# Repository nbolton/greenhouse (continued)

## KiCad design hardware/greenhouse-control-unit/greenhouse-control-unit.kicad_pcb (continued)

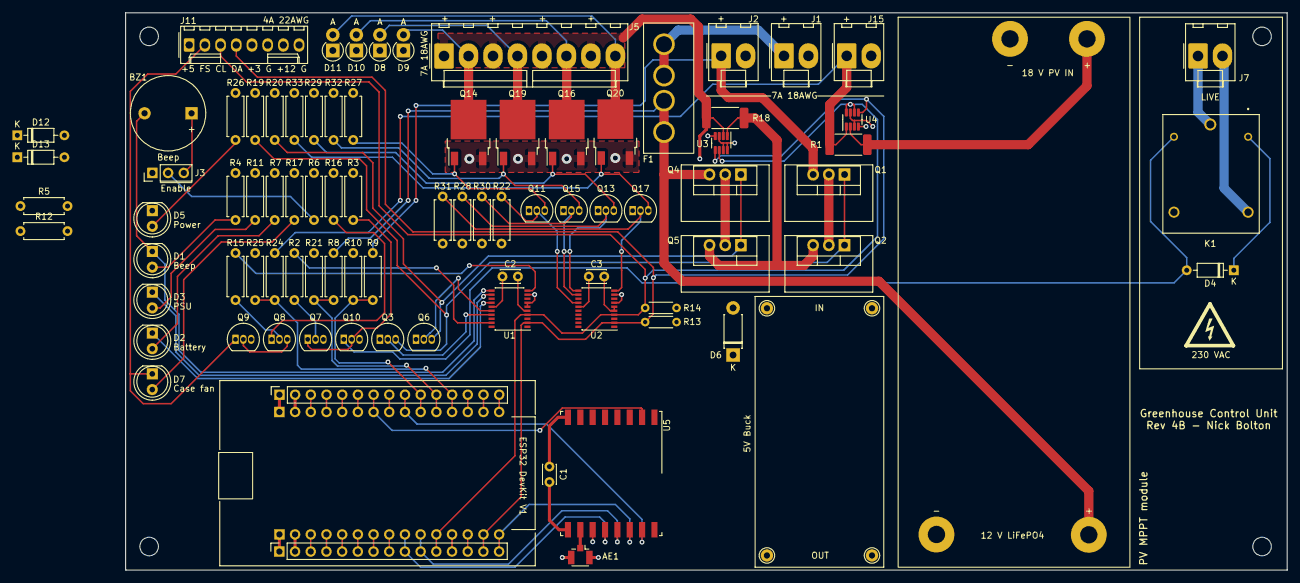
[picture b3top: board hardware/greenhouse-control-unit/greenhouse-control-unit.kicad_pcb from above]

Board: 4 copper layers, 188.0 x 90.2 mm, 89 parts (0 on the bottom side), 62 nets.

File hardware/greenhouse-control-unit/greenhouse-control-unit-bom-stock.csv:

Comment,Stock,Designator,Footprint,LCSC Part #
"2kΩ? Buzzer, polarized",5,BZ1,Buzzer_12x9.5RM7.6,
"10nF Unpolarized capacitor, small symbol",++,"C2,C3",C_Disc_D4.7mm_W2.5mm_P5.00mm,
LED Light emitting diode,++,"D1,D2,D3,D5,D7",LED_D5.0mm,
D Diode,++,D4,D_DO-35_SOD27_P7.62mm_Horizontal,
D Diode,++,D6,D_DO-41_SOD81_P7.62mm_Horizontal,
D Diode,++,"D8,D9,D10,D11",D_DO-41_SOD81_P2.54mm_Vertical_AnodeUp,
Fuse Fuse,++,F1,Fuse_3522-2_L,
"Molex_KK-396_01x02 Generic connector, single row, 01x02, script generated",10?,"J1,J2,J7,J15",Molex_KK-396_1x02_P3.96mm_Vertical,
"Beep_Jumper Generic connector, single row, 01x03, script generated",++,J3,PinHeader_1x03_P2.54mm_Vertical,
"PV MPPT module Generic connector, single row, 01x04, script generated",1,J4,MPPT-10A-Module,
"Conn_01x08_Pin Generic connector, single row, 01x08, script generated",-,J5,Molex_KK-396_1x08_P3.96mm_Vertical,
"5V Buck Generic connector, single row, 01x04, script generated",1?,J6,Buck_Module,
"Conn_01x09 Generic connector, single row, 01x09, script generated",-,J8,PinSocket_1x09_P2.54mm_Vertical,
"Conn_01x05_Female Generic connector, single row, 01x05, script generated",-,J9,PinSocket_1x05_P2.54mm_Vertical,
"Conn_ESP32_DevKitV1_Female Generic connector, single row, 01x13, script generated (kicad-library-utils/schlib/autogen/connector/)",-,J10,PinSocket_ESP32_DevKitV1,
"Molex_254_1x08 Generic connector, single row, 01x12, script generated (kicad-library-utils/schlib/autogen/connector/)",10?,J11,Molex_KK-254_AE-6410-08A_1x08_P2.54mm_Vertical,
"SRD-12VDC-SL-C Sanyo SRD relay, Single Pole Miniature Power Relay,",5,K1,Relay_SRD-12VDC-SL-C,
"IRF4905 -74A Id, -55V Vds, Single P-Channel HEXFET Power MOSFET, 20mOhm Ron, TO-220AB",50?,"Q1,Q2,Q4,Q5",TO-220-3_Vertical,
"2N7000 0.2A Id, 200V Vds, N-Channel MOSFET, 2.6V Logic Level, TO-92",10?,"Q3,Q6,Q11,Q13,Q15,Q17",TO-92_Inline,
"BC547 0.1A Ic, 45V Vce, Small Signal NPN Transistor, TO-92",10?,"Q7,Q8,Q10",TO-92_Inline,
"BC337 0.8A Ic, 45V Vce, NPN Transistor, TO-92",10?,Q9,TO-92_Inline,
"STD30NF06LT4 N-MOSFET transistor, gate/drain/source",0,"Q14,Q16,Q19,Q20",TO-252-2,
"0R001 Resistor, US symbol",0,"R1,R18",R_2512_6332Metric_Pad1.40x3.35mm_HandSolder,
"33k Resistor, US symbol",50?,"R2,R15",R_Axial_DIN0207_L6.3mm_D2.5mm_P7.62mm_Horizontal,
"1k Resistor, US symbol",50?,"R3,R16",R_Axial_DIN0207_L6.3mm_D2.5mm_P7.62mm_Horizontal,
"2k Resistor, US symbol",50?,"R4,R7,R11,R17",R_Axial_DIN0207_L6.3mm_D2.5mm_P7.62mm_Horizontal,
"100R Resistor, US symbol",50?,R6,R_Axial_DIN0207_L6.3mm_D2.5mm_P7.62mm_Horizontal,
"1M Resistor, US symbol",50?,"R8,R9,R24",R_Axial_DIN0207_L6.3mm_D2.5mm_P7.62mm_Horizontal,
"100k Resistor, US symbol",50?,"R10,R21,R25",R_Axial_DIN0207_L6.3mm_D2.5mm_P7.62mm_Horizontal,
"10k Resistor, US symbol",50?,"R13,R14",R_Axial_DIN0204_L3.6mm_D1.6mm_P5.08mm_Horizontal,
"10k Resistor, US symbol",50?,"R19,R22,R23,R26,R27,R28,R29,R30,R31,R32,R33",R_Axial_DIN0207_L6.3mm_D2.5mm_P7.62mm_Horizontal,
"PCF8574 8 Bit Port/Expander to I2C Bus, DIP/SOIC-16",0,"U1,U2",SOIC-16W_7.5x10.3mm_P1.27mm,
"INA219 Zero-Drift, Bidirectional Current/Power Monitor (0-26V) With I2C Interface, SOT-23-8",0,"U3,U4",SOT-23-8,

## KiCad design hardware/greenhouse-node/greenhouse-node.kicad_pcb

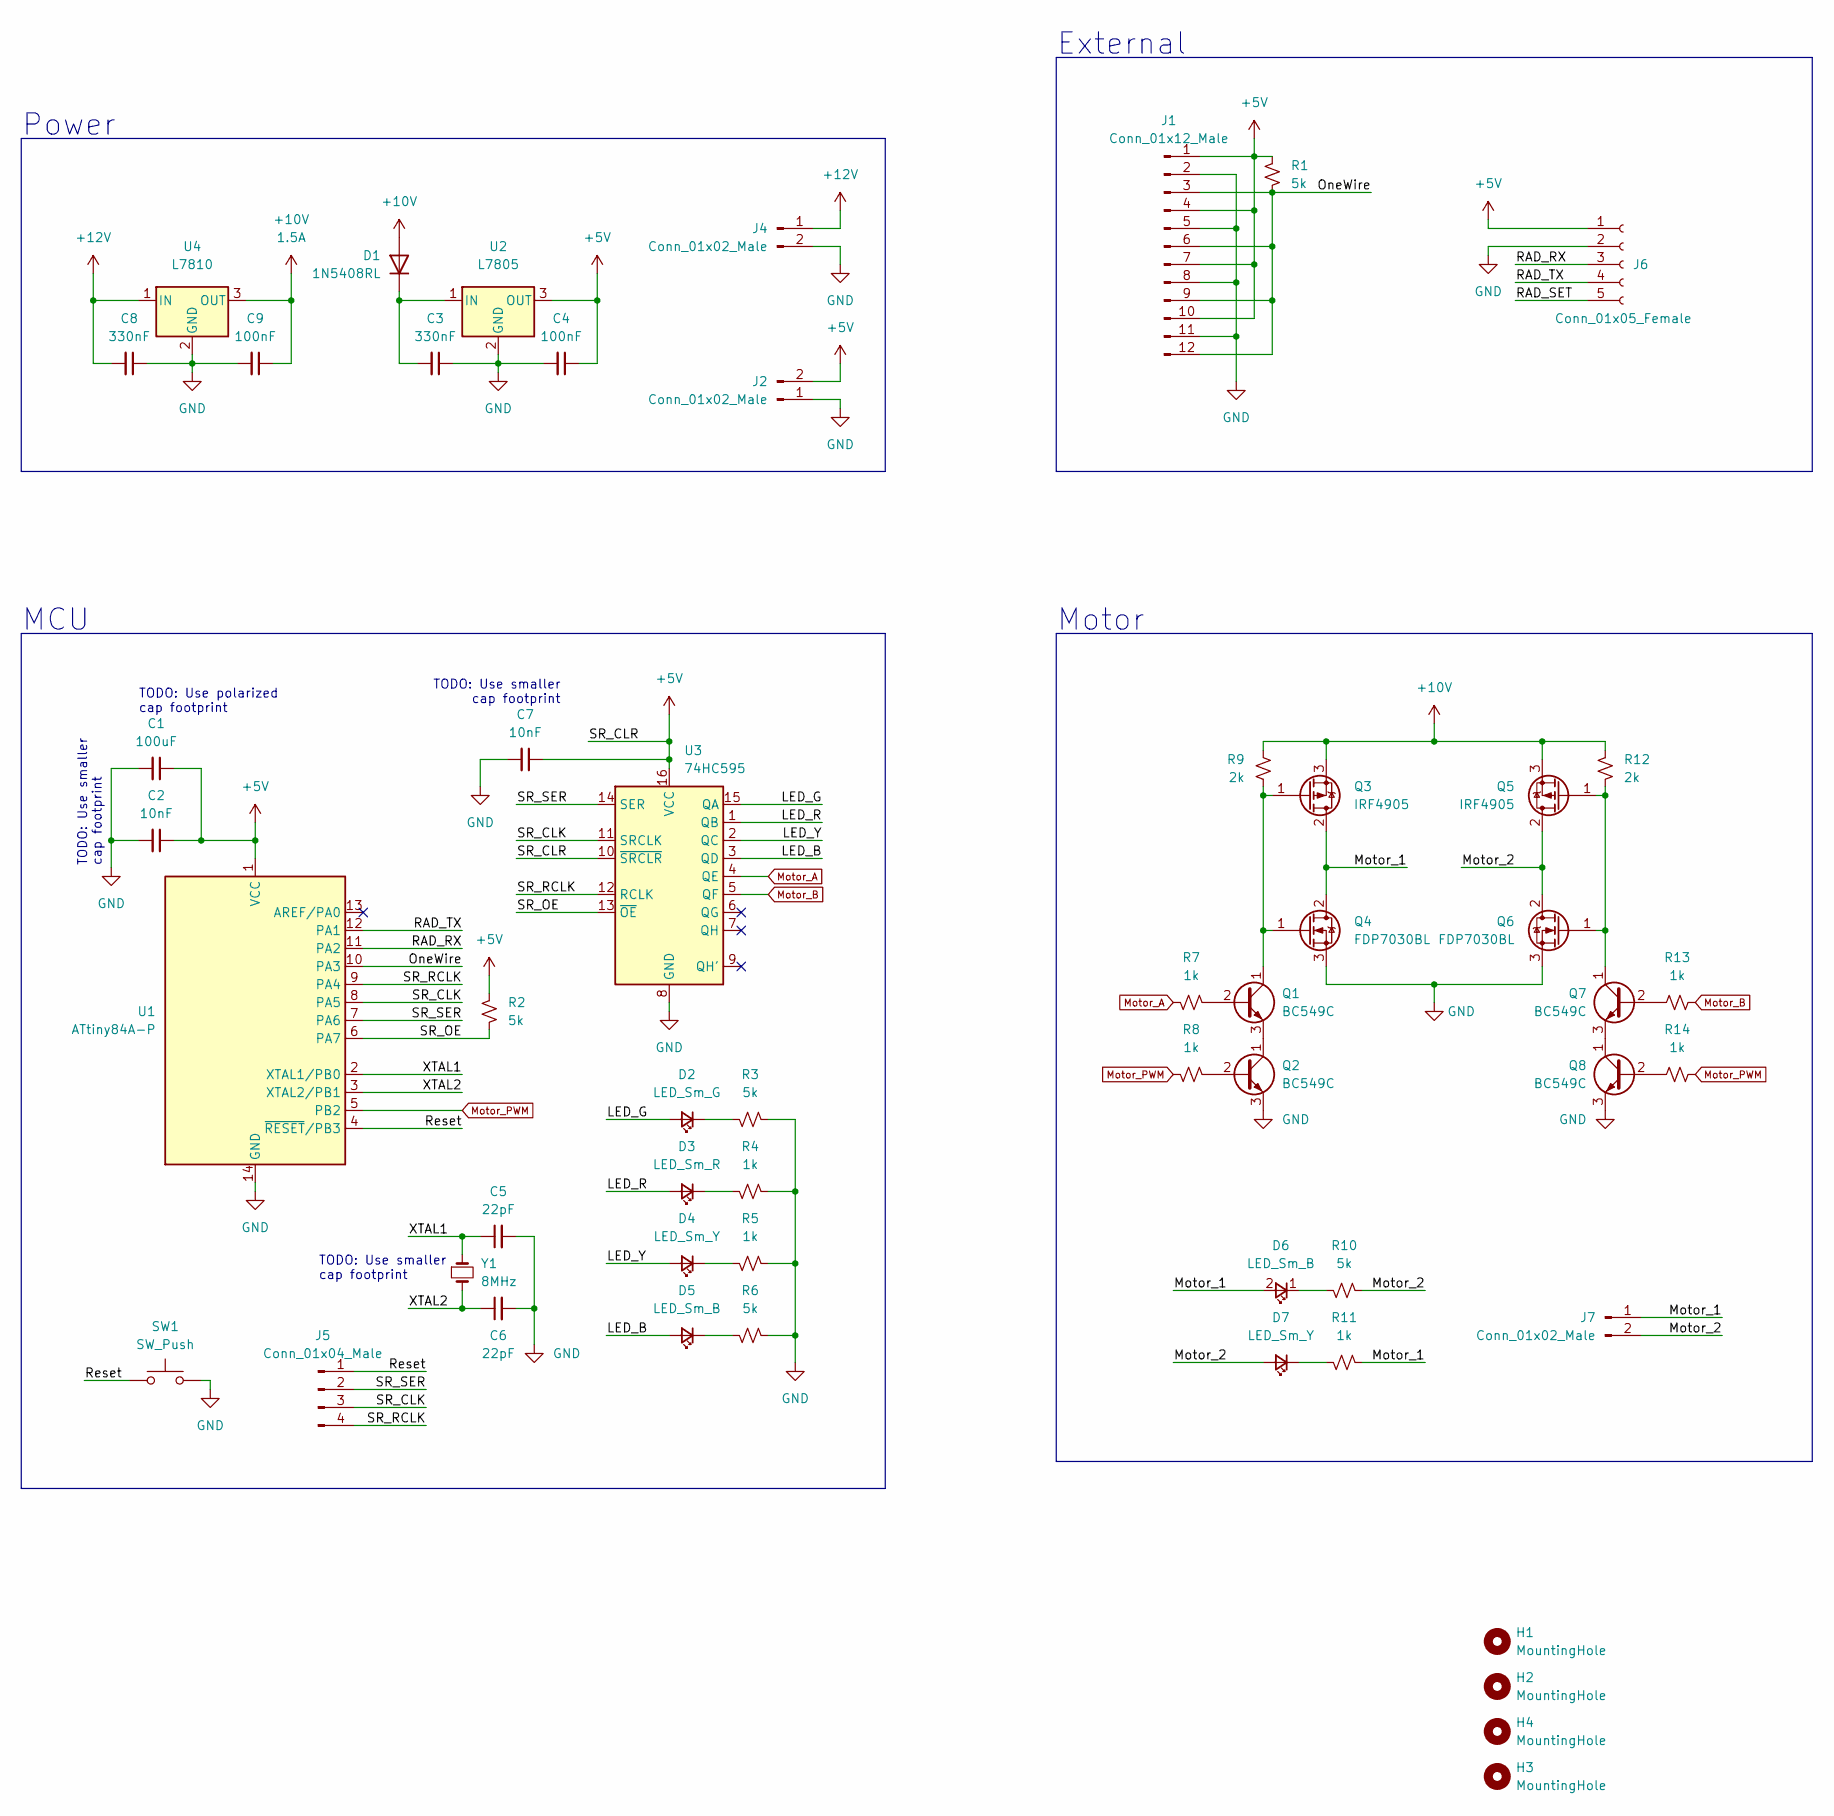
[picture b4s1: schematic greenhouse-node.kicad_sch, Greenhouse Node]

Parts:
C1: 100uF; C_Radial_D5.0mm_H7.0mm_P2.00mm
C2, C7: 10nF; C_Disc_D4.7mm_W2.5mm_P5.00mm
C3, C8: 330nF; C_Disc_D4.7mm_W2.5mm_P5.00mm
C4, C9: 100nF; C_Disc_D4.7mm_W2.5mm_P5.00mm
C5, C6: 22pF; C_Disc_D4.7mm_W2.5mm_P5.00mm
D1: 1N5408RL; D_A-405_P7.62mm_Horizontal
D2: LED_Sm_G; LED_D3.0mm
D3: LED_Sm_R; LED_D3.0mm
D4, D7: LED_Sm_Y; LED_D3.0mm
D5, D6: LED_Sm_B; LED_D3.0mm
H1, H2, H3, H4: MountingHole; MountingHole_3.2mm_M3
J1: Conn_01x12_Male; Molex_KK-254_AE-6410-12A_1x12_P2.54mm_Vertical
J2: Conn_01x02_Male; JST_XH_B2B-XH-A_1x02_P2.50mm_Vertical
J4, J7: Conn_01x02_Male; Molex_KK-396_A-41791-0002_1x02_P3.96mm_Vertical
J5: Conn_01x04_Male; JST_XH_B4B-XH-A_1x04_P2.50mm_Vertical
J6: Conn_01x05_Female; PinSocket_1x05_P2.54mm_Vertical
Q1, Q2, Q7, Q8: BC549C; TO-92_Inline
Q3, Q5: IRF4905; TO-220-3_Horizontal_TabDown
Q4, Q6: FDP7030BL; TO-220-3_Horizontal_TabDown
R1, R2, R3, R6, R10: 5k; R_Axial_DIN0207_L6.3mm_D2.5mm_P7.62mm_Horizontal
R4, R5, R7, R8, R11, R13, R14: 1k; R_Axial_DIN0207_L6.3mm_D2.5mm_P7.62mm_Horizontal
R9, R12: 2k; R_Axial_DIN0207_L6.3mm_D2.5mm_P7.62mm_Horizontal
SW1: SW_Push; SW_PUSH_6mm
U1: ATtiny84A-P; DIP-14_W7.62mm_Socket
U2: L7805; TO-220-3_Horizontal_TabDown
U3: 74HC595; DIP-16_W7.62mm_Socket
U4: L7810; TO-220-3_Horizontal_TabDown
Y1: 8MHz; Crystal_HC49-4H_Vertical

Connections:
+5V: C1.1, C2.1, C4.1, C7.1, J1.1, J1.4, J1.7, J1.10, J2.2, J6.1, R1.1, R2.1, U1.1 (VCC), U2.3 (OUT), U3.10 (~SRCLR), U3.16 (VCC)
+10V: C9.1, D1.2 (A), Q3.3 (S), Q5.3 (S), R9.2, R12.2, U4.3 (OUT)
+12V: C8.2, J4.1, U4.1 (IN)
/LED_B: D5.2 (A), U3.3 (QD)
/LED_G: D2.2 (A), U3.15 (QA)
/LED_R: D3.2 (A), U3.1 (QB)
/LED_Y: D4.2 (A), U3.2 (QC)
/Motor_1: D6.2 (A), J7.1, Q3.2 (D), Q4.2 (D), R11.1
/Motor_2: D7.2 (A), J7.2, Q5.2 (D), Q6.2 (D), R10.1
/OneWire: J1.3, J1.6, J1.9, J1.12, R1.2, U1.10 (PA3)
/RAD_RX: J6.3, U1.11 (PA2)
/RAD_SET: J6.5
/RAD_TX: J6.4, U1.12 (PA1)
/Reset: J5.1, SW1.1, U1.4 (~RESET/PB3)
/SR_CLK: J5.3, U1.8 (PA5), U3.11 (SRCLK)
/SR_OE: R2.2, U1.6 (PA7), U3.13 (~OE)
/SR_RCLK: J5.4, U1.9 (PA4), U3.12 (RCLK)
/SR_SER: J5.2, U1.7 (PA6), U3.14 (SER)
/XTAL1: C5.1, U1.2 (XTAL1/PB0), Y1.1
/XTAL2: C6.1, U1.3 (XTAL2/PB1), Y1.2
GND: C1.2, C2.2, C3.1, C4.2, C5.2, C6.2, C7.2, C8.1, C9.2, J1.2, J1.5, J1.8, J1.11, J2.1, J4.2, J6.2, Q2.3 (E), Q4.3 (S), Q6.3 (S), Q8.3 (E), R3.1, R4.1, R5.1, R6.1, SW1.2, U1.14 (GND), U2.2 (GND), U3.8 (GND), U4.2 (GND)
Motor_A: R7.2, U3.4 (QE)
Motor_B: R13.2, U3.5 (QF)
Motor_PWM: R8.2, R14.2, U1.5 (PB2)
unnamed: C3.2, D1.1 (K), U2.1 (IN)
unnamed: D2.1 (K), R3.2
unnamed: D3.1 (K), R4.2
unnamed: D4.1 (K), R5.2
unnamed: D5.1 (K), R6.2
unnamed: D6.1 (K), R10.2
unnamed: D7.1 (K), R11.2
unnamed: Q1.1 (C), Q3.1 (G), Q4.1 (G), R9.1
unnamed: Q1.2 (B), R7.1
unnamed: Q1.3 (E), Q2.1 (C)
unnamed: Q2.2 (B), R8.1
unnamed: Q5.1 (G), Q6.1 (G), Q7.1 (C), R12.1
unnamed: Q7.2 (B), R13.1
unnamed: Q7.3 (E), Q8.1 (C)
unnamed: Q8.2 (B), R14.1

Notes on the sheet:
Motor
TODO: Use polarized cap footprint
Power
MCU
TODO: Use smaller cap footprint
External

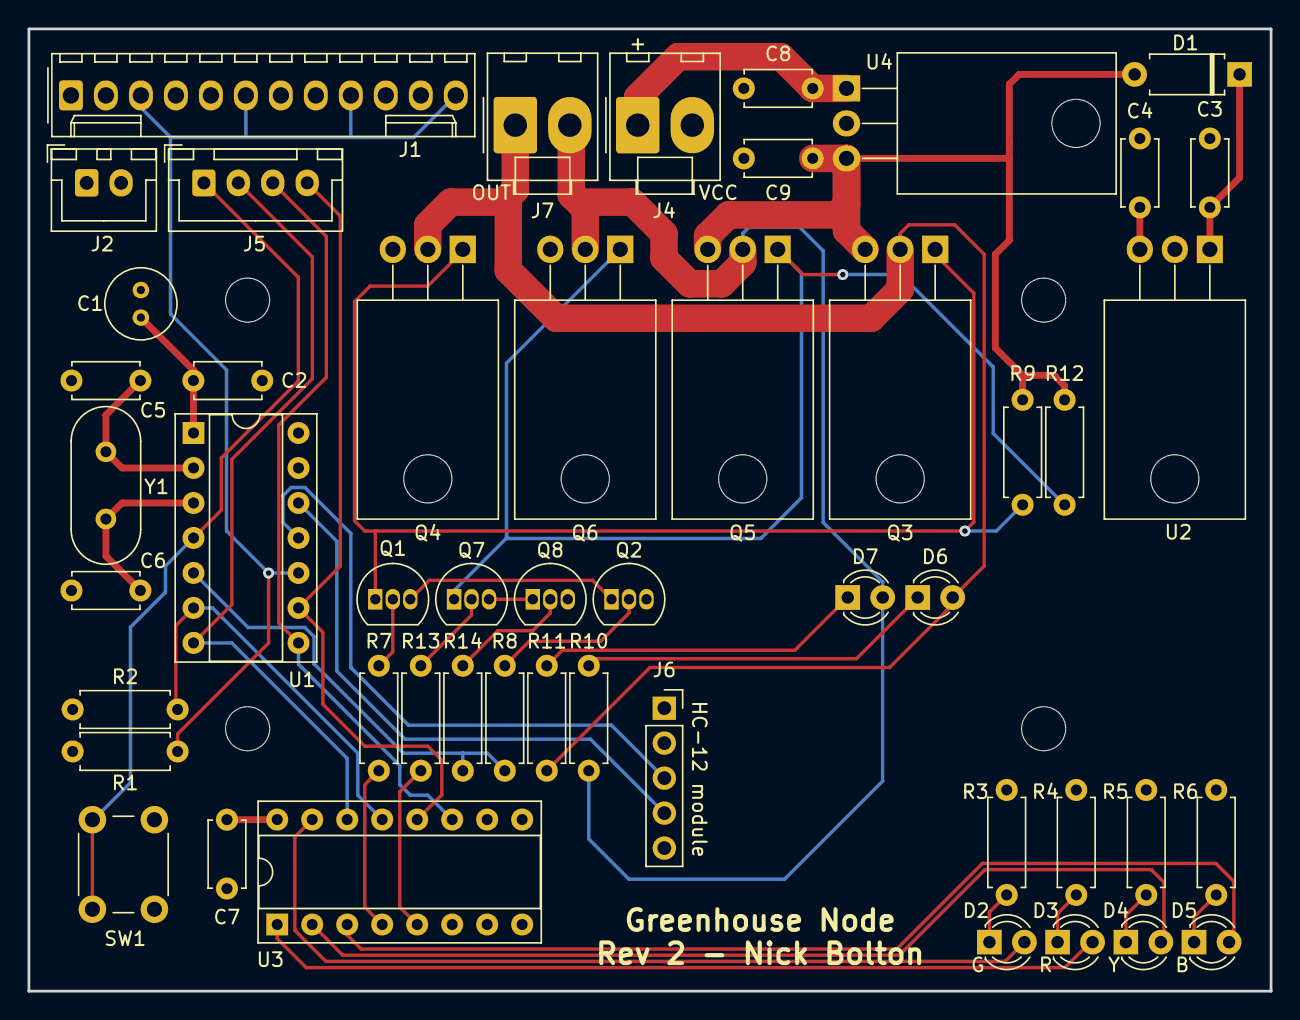
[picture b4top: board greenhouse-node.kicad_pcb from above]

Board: 4 copper layers, 90.2 x 69.8 mm, 54 parts (0 on the bottom side), 38 nets.

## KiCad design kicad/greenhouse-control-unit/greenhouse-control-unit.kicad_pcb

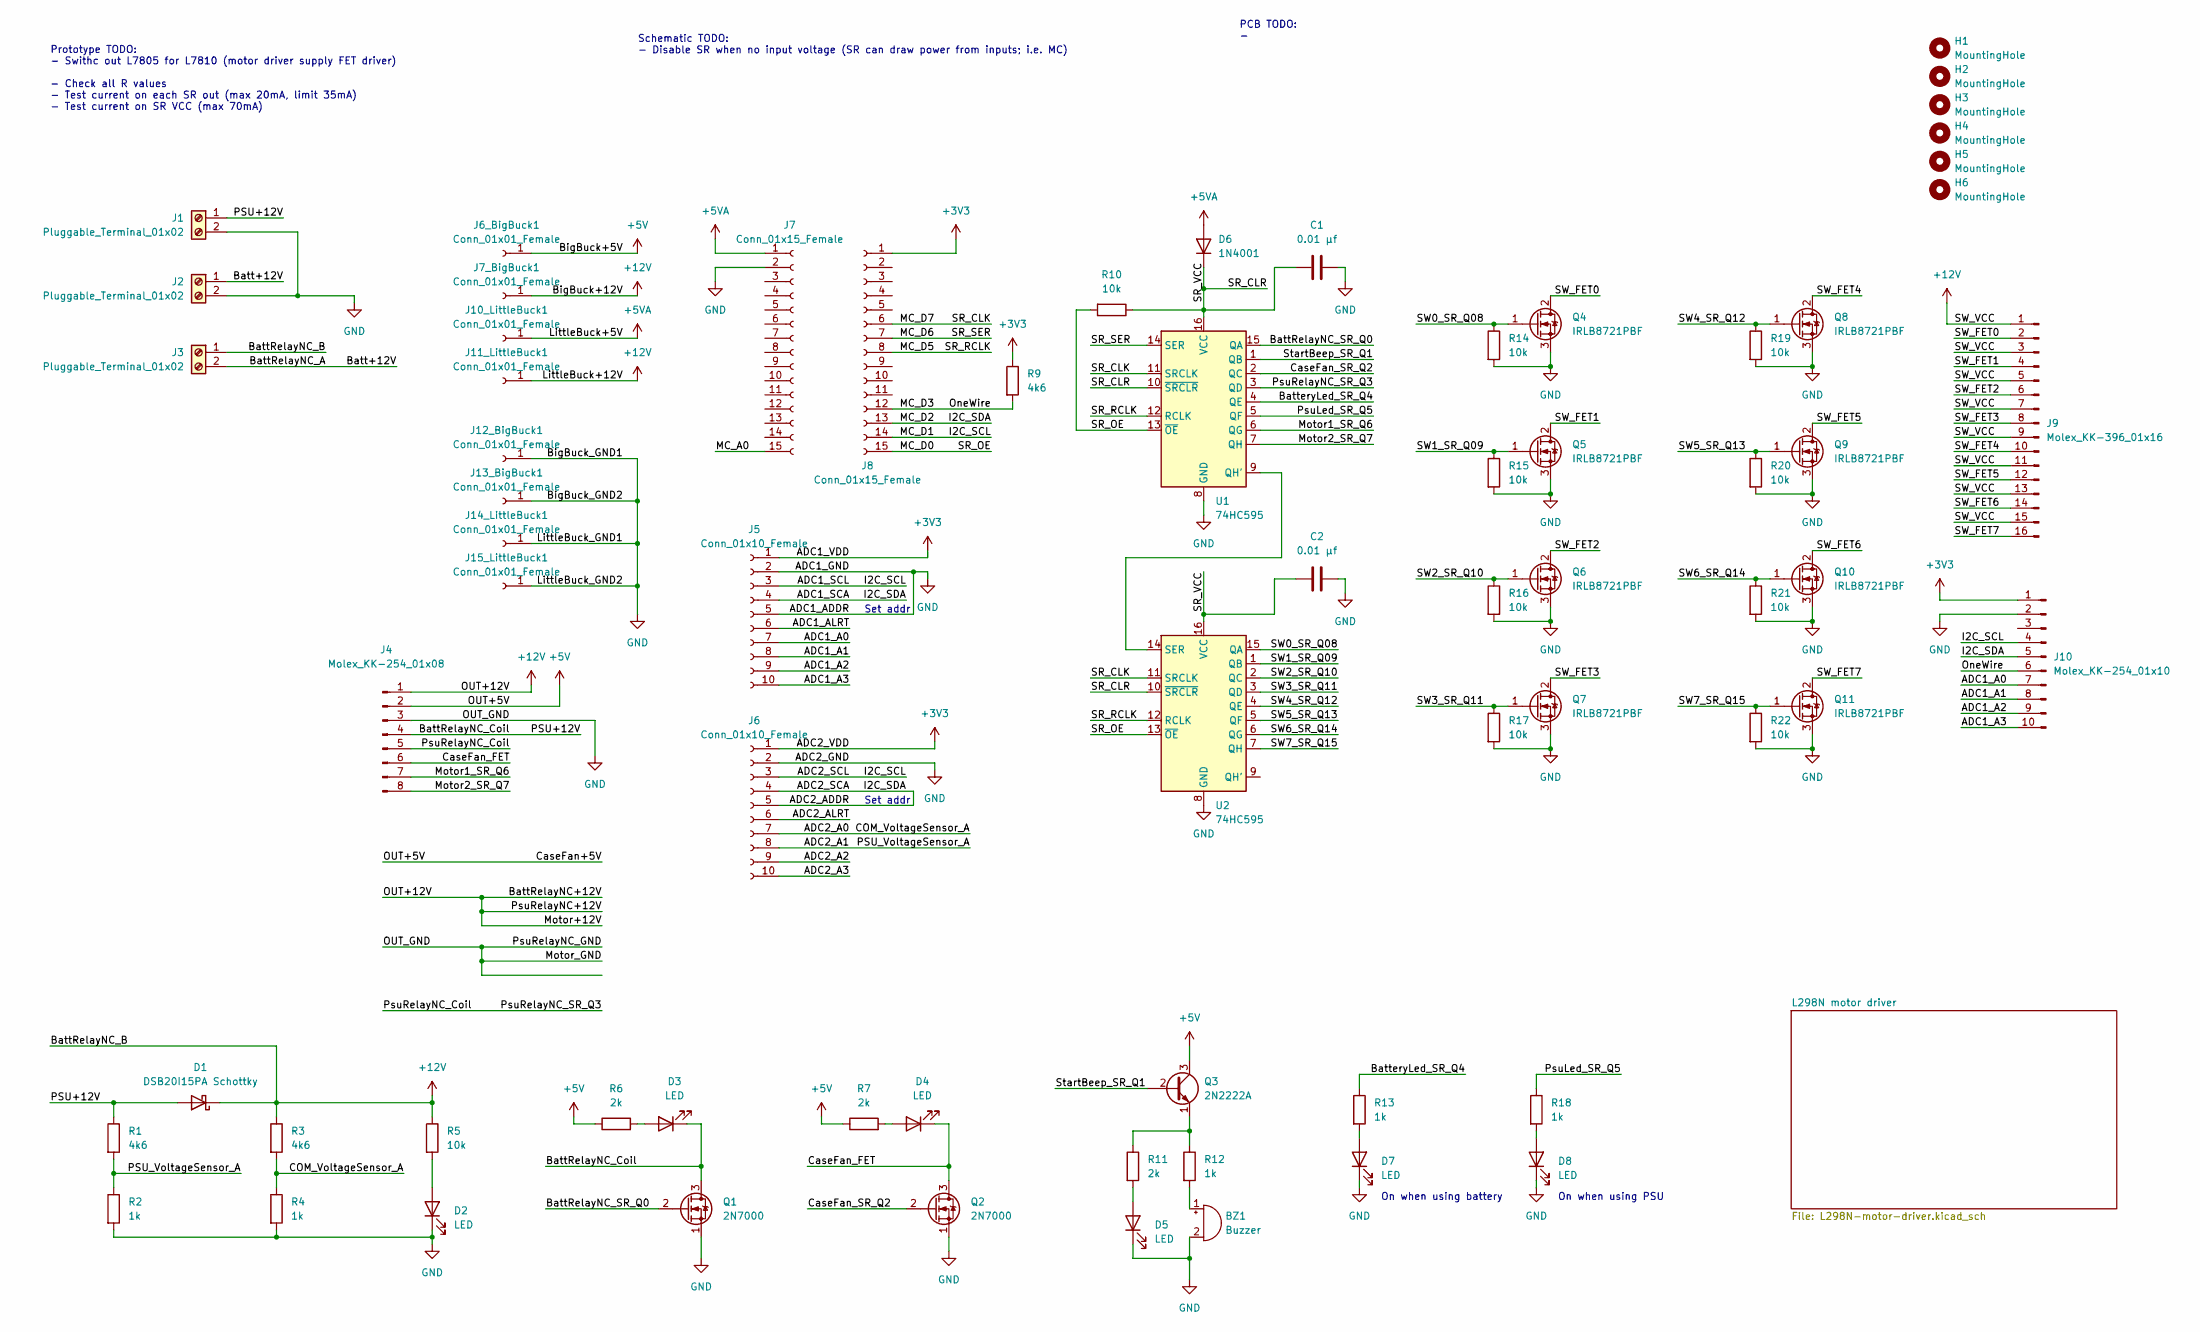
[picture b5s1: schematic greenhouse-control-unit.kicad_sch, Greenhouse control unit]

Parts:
BZ1: Buzzer; Buzzer_12x9.5RM7.6
C1, C2: 0.01 μf; C_Disc_D3.0mm_W1.6mm_P2.50mm
D1: DSB20I15PA Schottky; TO-220-2_Vertical
D2, D3, D4, D5, D7, D8: LED; LED_D5.0mm
D6: 1N4001; D_DO-41_SOD81_P10.16mm_Horizontal
H1, H2, H3, H4, H5, H6: MountingHole; MountingHole_3mm
J1, J2, J3: Pluggable_Terminal_01x02; TerminalBlock_Phoenix_MKDS-1,5-2-5.08_1x02_P5.08mm_Horizont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
J4: Molex_KK-254_01x08; Molex_KK-254_AE-6410-08A_1x08_P2.54mm_Vertical
J5, J6: Conn_01x10_Female; PinSocket_1x10_P2.54mm_Vertical
J6_BigBuck1, J7_BigBuck1, J12_BigBuck1, J13_BigBuck1: Conn_01x01_Female; PinSocket_1x01_P2.54mm_Vertical
J7, J8: Conn_01x15_Female; PinSocket_1x15_P2.54mm_Vertical
J9: Molex_KK-396_01x16; Molex_KK-396_A-41791-0016_1x16_P3.96mm_Vertical
J10: Molex_KK-254_01x10; Molex_KK-254_AE-6410-10A_1x10_P2.54mm_Vertical
J10_LittleBuck1, J11_LittleBuck1, J14_LittleBuck1, J15_LittleBuck1: Conn_01x01_Female; PinHeader_1x01_P2.54mm_Vertical
Q1, Q2: 2N7000; TO-92_Inline
Q3: 2N2222A; TO-92_Inline
Q4, Q5, Q6, Q7, Q8, Q9, Q10, Q11: IRLB8721PBF; TO-220-3_Horizontal_TabDown
R1, R3, R9: 4k6; R_Axial_DIN0207_L6.3mm_D2.5mm_P7.62mm_Horizontal
R2, R4, R12, R13, R18: 1k; R_Axial_DIN0207_L6.3mm_D2.5mm_P7.62mm_Horizontal
R5: 10k; R_Axial_DIN0207_L6.3mm_D2.5mm_P7.62mm_Horizontal
R6, R7, R11: 2k; R_Axial_DIN0207_L6.3mm_D2.5mm_P7.62mm_Horizontal
R10, R14, R15, R16, R17, R19, R20, R21, R22: 10k; R_Axial_DIN0204_L3.6mm_D1.6mm_P5.08mm_Horizontal
U1, U2: 74HC595; DIP-16_W7.62mm_Socket

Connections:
+3V3: J5.1, J6.1, J8.1, J10.1, R9.1
+5V: J4.2, J6_BigBuck1.1, Q3.3 (C), R6.1, R7.1; also elsewhere on the board
+5VA: D6.2 (A), J7.1, J10_LittleBuck1.1
+12V: D1.1 (K), J3.1, J4.1, J7_BigBuck1.1, J9.1, J9.3, J9.5, J9.7, J9.9, J9.11, J9.13, J9.15, J11_LittleBuck1.1, R3.1, R5.1; also elsewhere on the board
/ADC1_A0: J5.7, J10.7
/ADC1_A1: J5.8, J10.8
/ADC1_A2: J5.9, J10.9
/ADC1_A3: J5.10, J10.10
/ADC1_ALRT: J5.6
/ADC1_SCA: J5.4, J6.4, J6.5, J8.13, J10.5
/ADC1_SCL: J5.3, J6.3, J8.14, J10.4
/ADC2_A0: J6.7, R3.2, R4.1
/ADC2_A1: J6.8, R1.2, R2.1
/ADC2_A2: J6.9
/ADC2_A3: J6.10
/ADC2_ALRT: J6.6
/Batt+12V: J2.1, J3.2
/BattRelayNC_Coil: D1.2 (A), D3.1 (K), J1.1, J4.4, Q1.3 (D), R1.1
/BattRelayNC_SR_Q0: Q1.2 (G), U1.15 (QA)
/BatteryLed_SR_Q4: R13.1, U1.4 (QE)
/CaseFan_FET: D4.1 (K), J4.6, Q2.3 (D)
/CaseFan_SR_Q2: Q2.2 (G), U1.2 (QC)
/MC_A0: J7.15
/MC_D0: J8.15, R10.2, U1.13 (~OE), U2.13 (~OE)
/MC_D3: J8.12, J10.6, R9.2
/MC_D5: J8.8, U1.12 (RCLK), U2.12 (RCLK)
/MC_D6: J8.7, U1.14 (SER)
/MC_D7: J8.6, U1.11 (SRCLK), U2.11 (SRCLK)
/Motor1_SR_Q6: J4.7, U1.6 (QG)
/Motor2_SR_Q7: J4.8, U1.7 (QH)
/PsuLed_SR_Q5: R18.1, U1.5 (QF)
/PsuRelayNC_Coil: J4.5, U1.3 (QD)
/SR_CLR: C1.1, C2.1, D6.1 (K), R10.1, U1.10 (~SRCLR), U1.16 (VCC), U2.10 (~SRCLR), U2.16 (VCC)
/SW0_SR_Q08: Q4.1 (G), R14.1, U2.15 (QA)
/SW1_SR_Q09: Q5.1 (G), R15.1, U2.1 (QB)
/SW2_SR_Q10: Q6.1 (G), R16.1, U2.2 (QC)
/SW3_SR_Q11: Q7.1 (G), R17.1, U2.3 (QD)
/SW4_SR_Q12: Q8.1 (G), R19.1, U2.4 (QE)
/SW5_SR_Q13: Q9.1 (G), R20.1, U2.5 (QF)
/SW6_SR_Q14: Q10.1 (G), R21.1, U2.6 (QG)
/SW7_SR_Q15: Q11.1 (G), R22.1, U2.7 (QH)
/SW_FET0: J9.2, Q4.2 (D)
/SW_FET1: J9.4, Q5.2 (D)
/SW_FET2: J9.6, Q6.2 (D)
/SW_FET3: J9.8, Q7.2 (D)
/SW_FET4: J9.10, Q8.2 (D)
/SW_FET5: J9.12, Q9.2 (D)
/SW_FET6: J9.14, Q10.2 (D)
/SW_FET7: J9.16, Q11.2 (D)
/StartBeep_SR_Q1: Q3.2 (B), U1.1 (QB)
GND: BZ1.2 (+), C1.2, C2.2, D2.1 (K), D5.1 (K), D7.1 (K), D8.1 (K), J1.2, J2.2, J4.3, J5.2, J5.5, J6.2, J7.2, J10.2, J12_BigBuck1.1, J13_BigBuck1.1, J14_LittleBuck1.1, J15_LittleBuck1.1, Q1.1 (S), Q2.1 (S), Q4.3 (S), Q5.3 (S), Q6.3 (S), Q7.3 (S), Q8.3 (S), Q9.3 (S), Q10.3 (S), Q11.3 (S), R2.2, R4.2, R14.2, R15.2, R16.2, R17.2, R19.2, R20.2, R21.2, R22.2, U1.8 (GND), U2.8 (GND); also elsewhere on the board
unnamed: BZ1.1 (-), R12.2
unnamed: D2.2 (A), R5.2
unnamed: D3.2 (A), R6.2
unnamed: D4.2 (A), R7.2
unnamed: D5.2 (A), R11.2
unnamed: D7.2 (A), R13.2
unnamed: D8.2 (A), R18.2
unnamed: Q3.1 (E), R11.1, R12.1
unnamed: U1.9 (QH'), U2.14 (SER)

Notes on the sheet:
On when using battery
PCB TODO: -
Set addr
On when using PSU
Schematic TODO: - Disable SR when no input voltage (SR can draw power from inputs; i.e. MC)
Prototype TODO: - Swithc out L7805 for L7810 (motor driver supply FET driver) - Check all R values - Test current on each SR out (max 20mA, limit 35mA) - Test current on SR VCC (max 70mA)

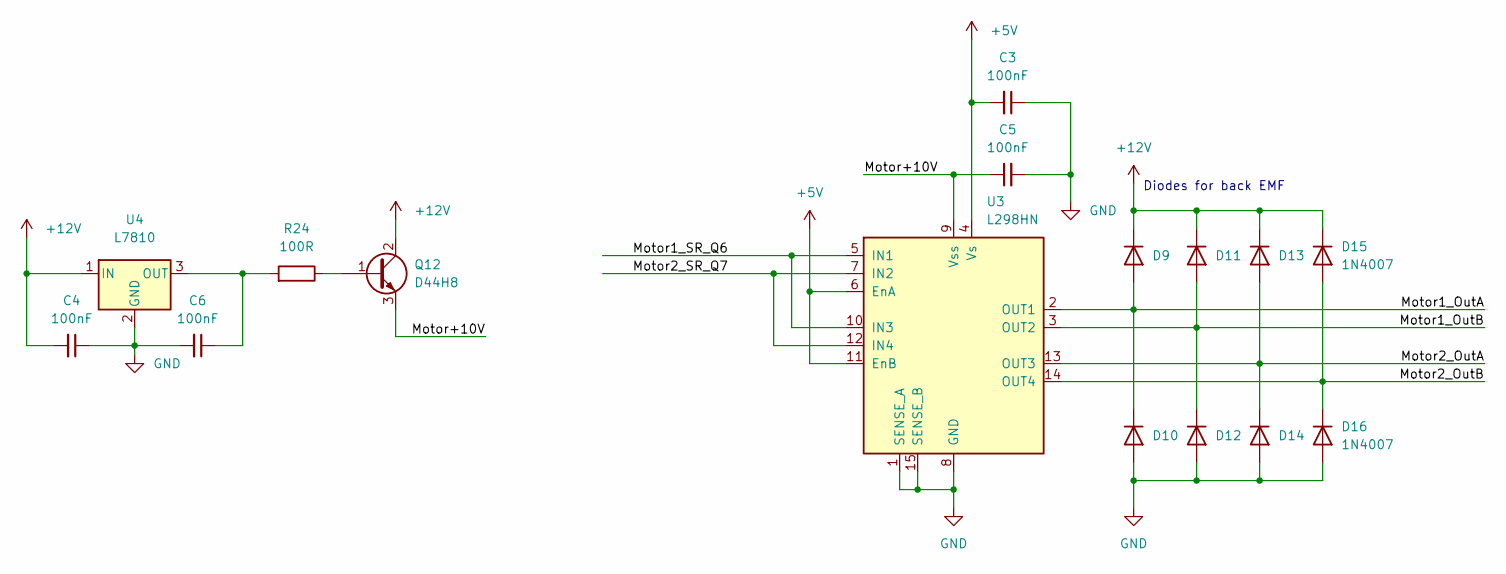
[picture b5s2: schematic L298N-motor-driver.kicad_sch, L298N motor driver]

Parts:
C3, C4, C5, C6: 100nF; C_Disc_D4.7mm_W2.5mm_P5.00mm
D9, D10, D11, D12, D13, D14, D15, D16: 1N4007; D_DO-41_SOD81_P10.16mm_Horizontal
Q12: D44H8; TO-220-3_Vertical
R24: 100R; R_Axial_DIN0204_L3.6mm_D1.6mm_P5.08mm_Horizontal
U3: L298HN; TO-220-15_P2.54x2.54mm_StaggerOdd_Lead4.58mm_Vertical
U4: L7810

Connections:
+5V: C3.2, U3.4 (Vs), U3.6 (EnA), U3.11 (EnB); also elsewhere on the board
+12V: C4.2, D9.1 (K), D11.1 (K), D13.1 (K), D15.1 (K), Q12.2 (C), U4.1 (IN); also elsewhere on the board
/L298N motor driver/Motor1_OutA: D9.2 (A), D10.1 (K), U3.2 (OUT1)
/L298N motor driver/Motor1_OutB: D11.2 (A), D12.1 (K), U3.3 (OUT2)
/L298N motor driver/Motor1_SR_Q6: U3.5 (IN1), U3.10 (IN3)
/L298N motor driver/Motor2_OutA: D13.2 (A), D14.1 (K), U3.13 (OUT3)
/L298N motor driver/Motor2_OutB: D15.2 (A), D16.1 (K), U3.14 (OUT4)
/L298N motor driver/Motor2_SR_Q7: U3.7 (IN2), U3.12 (IN4)
/L298N motor driver/Motor+10V: C5.1, Q12.3 (E), U3.9 (Vss)
GND: C3.1, C4.1, C5.2, C6.2, D10.2 (A), D12.2 (A), D14.2 (A), D16.2 (A), U3.1 (SENSE_A), U3.8 (GND), U3.15 (SENSE_B), U4.2 (GND); also elsewhere on the board
unnamed: C6.1, R24.2, U4.3 (OUT)
unnamed: Q12.1 (B), R24.1

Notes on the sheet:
Diodes for back EMF

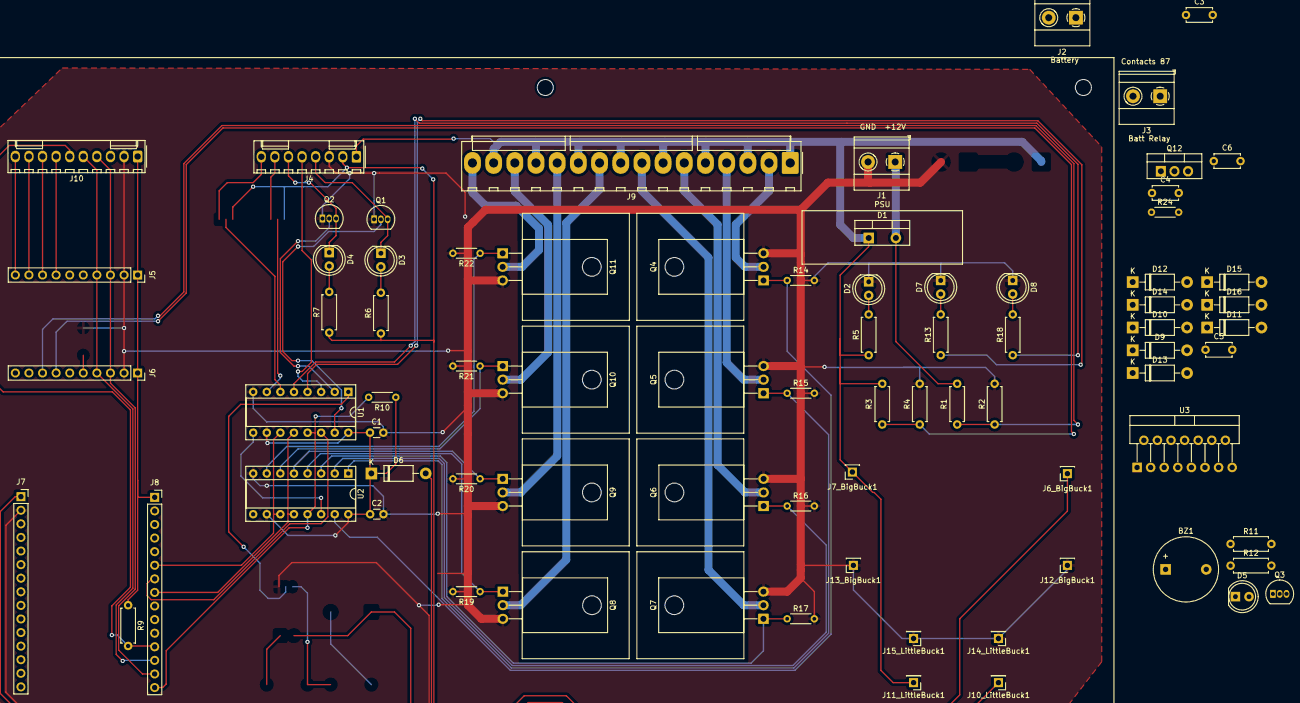
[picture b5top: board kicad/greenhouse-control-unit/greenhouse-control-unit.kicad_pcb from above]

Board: 2 copper layers, 84 parts (0 on the bottom side), 64 nets.

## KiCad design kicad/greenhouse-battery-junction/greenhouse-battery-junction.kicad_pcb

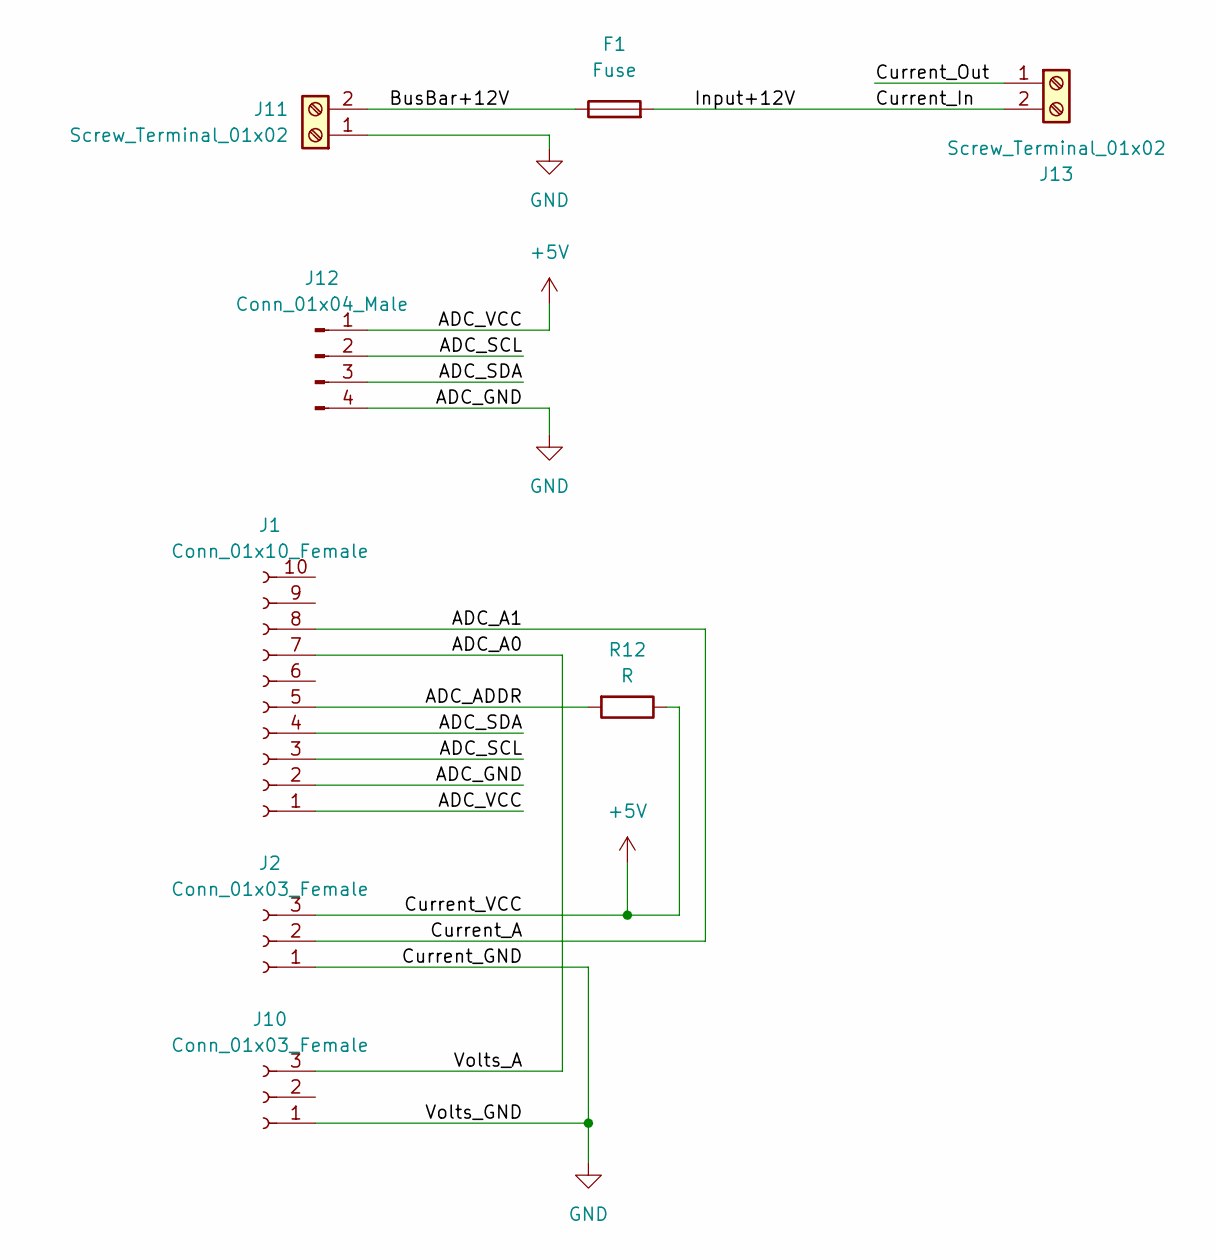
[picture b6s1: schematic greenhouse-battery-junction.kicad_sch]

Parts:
F1: Fuse; Fuse_Blade_Mini_directSolder
J1: Conn_01x10_Female; PinHeader_1x10_P2.54mm_Vertical
J2, J10: Conn_01x03_Female; PinHeader_1x03_P2.54mm_Vertical
J11, J13: Screw_Terminal_01x02; TerminalBlock_Phoenix_MKDS-1,5-2-5.08_1x02_P5.08mm_Horizont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
J12: Conn_01x04_Male; Molex_KK-254_AE-6410-04A_1x04_P2.54mm_Vertical
R12: R; R_Box_L8.4mm_W2.5mm_P5.08mm

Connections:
+5V: J1.1, J2.3, J12.1, R12.1
/ADC_A0: J1.7, J10.3
/ADC_A1: J1.8, J2.2
/ADC_ADDR: J1.5, R12.2
/ADC_SCL: J1.3, J12.2
/ADC_SDA: J1.4, J12.3
/BusBar+12V: F1.1, J11.2
/Current_In: F1.2, J13.2
/Current_Out: J13.1
GND: J1.2, J2.1, J10.1, J11.1, J12.4

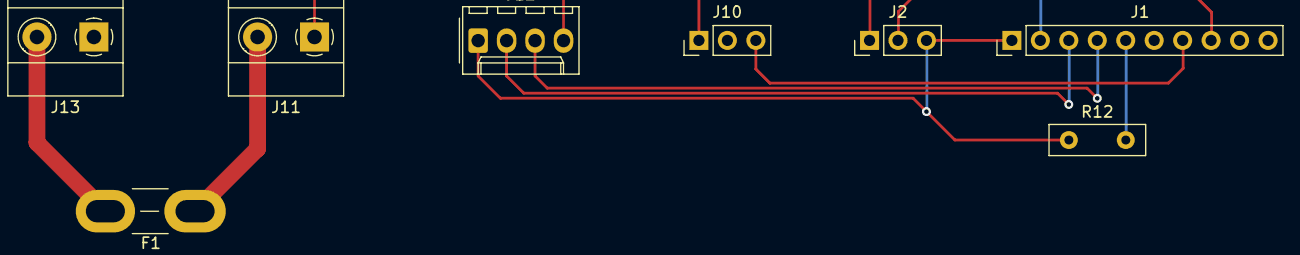
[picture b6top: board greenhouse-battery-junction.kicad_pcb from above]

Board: 2 copper layers, 8 parts (0 on the bottom side), 9 nets.

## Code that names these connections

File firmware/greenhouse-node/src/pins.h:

#pragma once

#include "attiny.h"

#define PIN_TX_EN PIN_PA0
#define PIN_TX PIN_PA1
#define PIN_RX PIN_PA2
#define PIN_ONE_WIRE PIN_PA3
#define PIN_SR_LATCH PIN_PA4  // RCLK (12)
#define PIN_SR_CLOCK PIN_PA5  // SRCLK (11)
#define PIN_SR_DATA PIN_PA6   // SER (14)
#define PIN_SR_OE PIN_PA7     // OE (13)
#define PIN_MOTOR_PWM PIN_PB2
